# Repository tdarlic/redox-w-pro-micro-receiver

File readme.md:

# [Redox](https://github.com/mattdibi/redox-keyboard) W Pro Micro receiver

The original Redox keyboard is using receiver that consists from the Arduino Pro Micro board and custom made "shield"
that is used to put few leds and a YJ-14015 module (Core51822B clone).

This PCB uses the on board copper connection to plug directly into the computer.
 
The rest of the board can be used the same way, there is a programming port for YJ-14015 module.

## Versions

### Full version [main branch]
This is single sided PCB with few test pads on the bottom

### Mini version [mini branch]
This is double sided PCB with YJ-14015 on the bottom together with some test pads

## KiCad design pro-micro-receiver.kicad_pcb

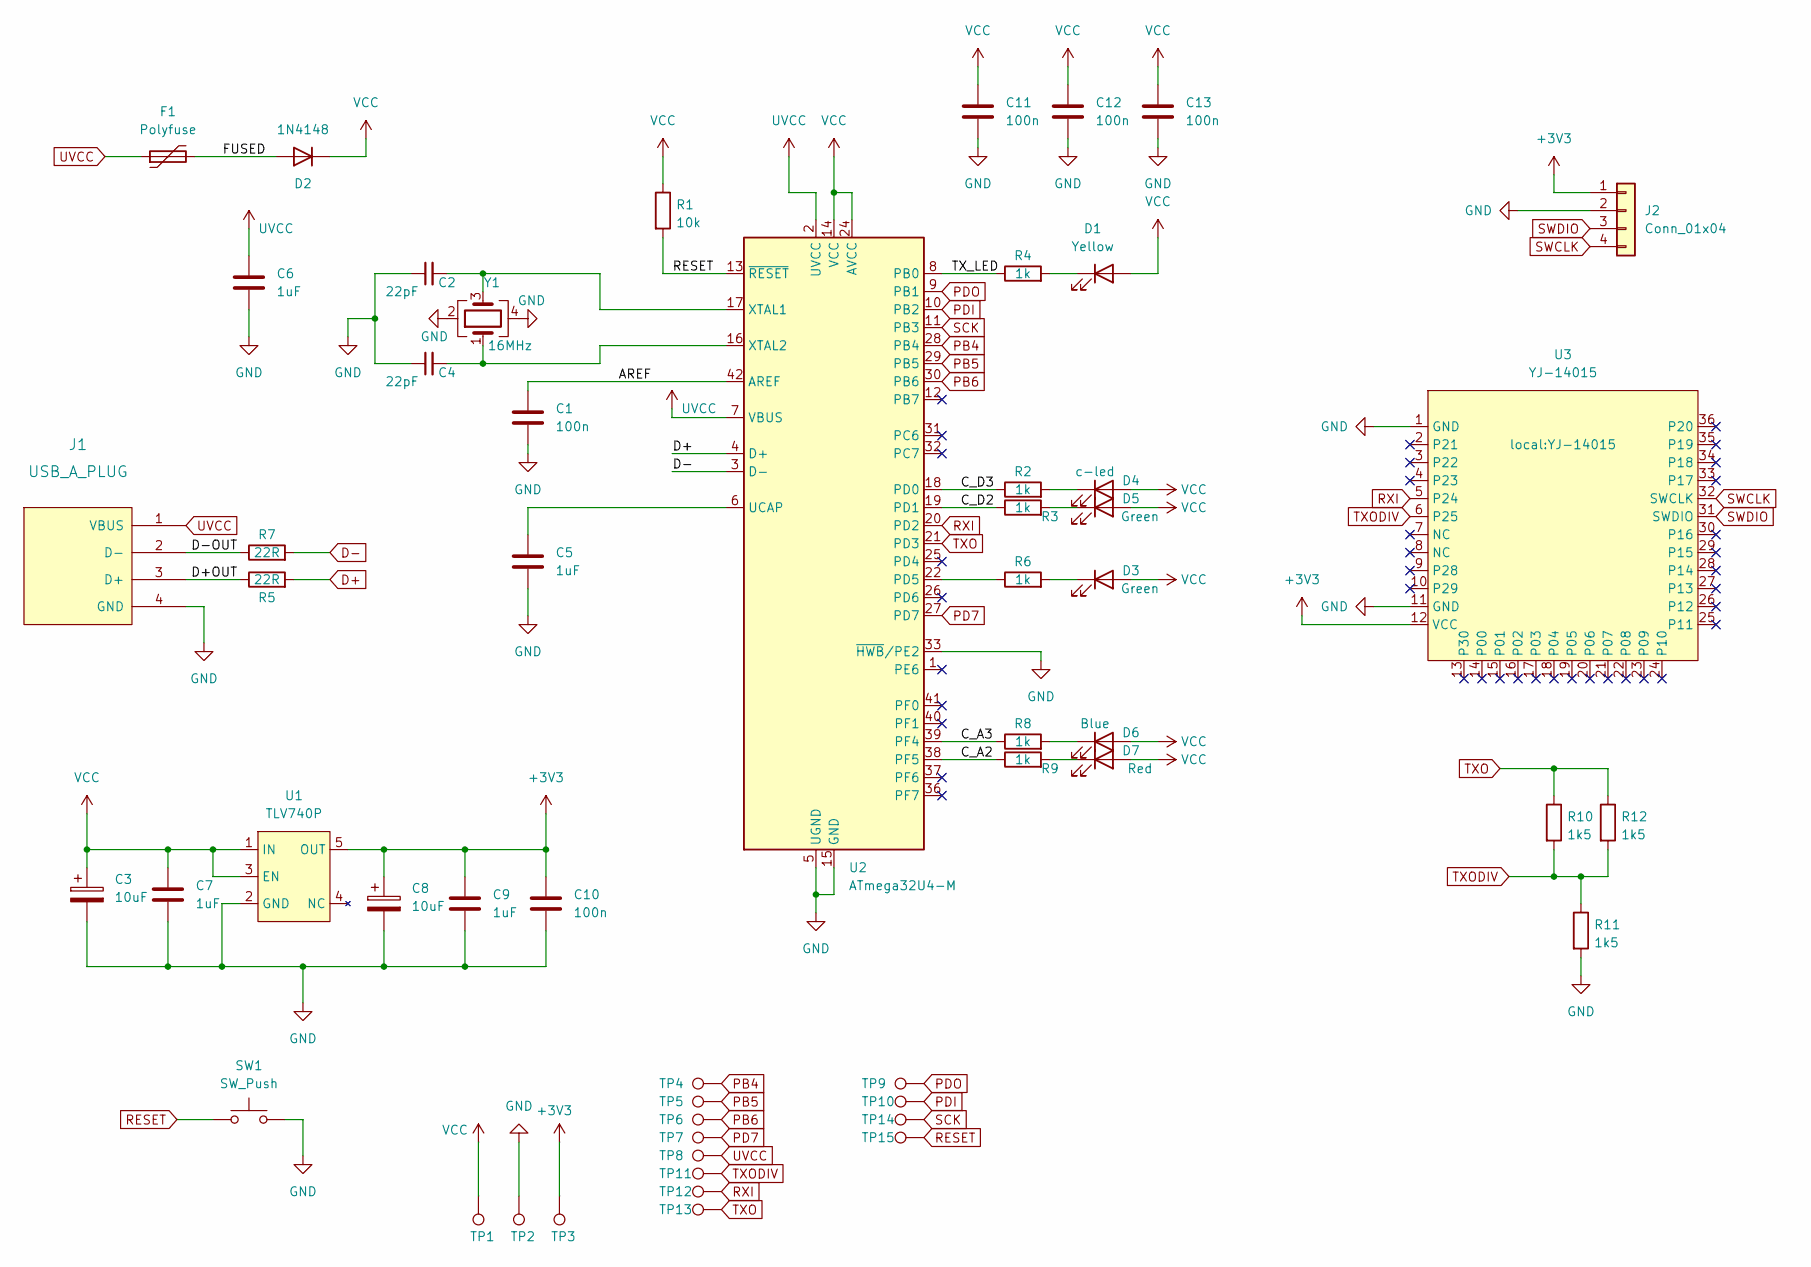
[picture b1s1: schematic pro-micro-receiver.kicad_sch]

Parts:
C1, C10, C11, C12, C13: 100n; C_0603_1608Metric
C2, C4: 22pF; C_0603_1608Metric
C3, C8: 10uF; CP_EIA-1608-10_AVX-L_Pad1.25x1.05mm
C5, C6, C7, C9: 1uF; C_0603_1608Metric
D1: Yellow; D_0603_1608Metric_Pad1.05x0.95mm
D2: 1N4148; D_SOD-123
D3, D5: Green; D_0603_1608Metric_Pad1.05x0.95mm
D4: c-led; D_0603_1608Metric_Pad1.05x0.95mm
D6: Blue; D_0603_1608Metric_Pad1.05x0.95mm
D7: Red; D_0603_1608Metric_Pad1.05x0.95mm
F1: Polyfuse; Fuse_1812_4532Metric
J1: USB_A_PLUG; usb-PCB
J2: Conn_01x04; PinHeader_1x04_P2.54mm_Vertical
R1: 10k; R_0603_1608Metric
R2, R3, R4, R6, R8, R9: 1k; R_0603_1608Metric
R5, R7: 22R; R_0603_1608Metric
R10, R11, R12: 1k5; R_0603_1608Metric
SW1: SW_Push; BZCN_TSB001A3512A
TP1, TP2, TP3, TP4, TP5, TP6, TP7, TP8, TP9, TP10, TP11, TP12, TP13, TP14, TP15: TestPoint; TestPoint_Pad_D1.5mm
U1: TLV740P; SOT-23-5
U2: ATmega32U4-M; QFN-44-1EP_7x7mm_P0.5mm_EP5.2x5.2mm
U3: YJ-14015
Y1: 16MHz; Crystal_SMD_EuroQuartz_MT-4Pin_3.2x2.5mm

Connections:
+3V3: C8.1, C9.1, C10.1, J2.1, TP3.1, U1.5 (OUT), U3.12 (VCC)
/AREF: C1.1, U2.42 (AREF)
/C_A2: R9.1, U2.38 (PF5)
/C_A3: R8.1, U2.39 (PF4)
/C_D2: R3.1, U2.19 (PD1)
/C_D3: R2.1, U2.18 (PD0)
/D+OUT: J1.3 (D+), R5.1
/D-OUT: J1.2 (D-), R7.1
/FUSED: D2.2 (A), F1.2
/TX_LED: R4.1, U2.8 (PB0)
D+: R5.2, U2.4 (D+)
D-: R7.2, U2.3 (D-)
GND: C1.2, C2.1, C3.2, C4.1, C5.2, C6.2, C7.2, C8.2, C9.2, C10.2, C11.2, C12.2, C13.2, J1.4 (GND), J2.2, R11.2, SW1.2, TP2.1, U1.2 (GND), U2.5 (UGND), U2.15 (GND), U2.23 (GND), U2.33 (~HWB/PE2), U2.35 (GND), U2.43 (GND), U2.45 (GND), U3.1 (GND), U3.11 (GND), Y1.2, Y1.4
unnamed: C2.2, U2.17 (XTAL1), Y1.3
unnamed: C4.2, U2.16 (XTAL2), Y1.1
unnamed: C5.1, U2.6 (UCAP)
unnamed: D1.1 (K), R4.2
unnamed: D3.1 (K), R6.2
unnamed: D4.1 (K), R2.2
unnamed: D5.1 (K), R3.2
unnamed: D6.1 (K), R8.2
unnamed: D7.1 (K), R9.2
unnamed: R6.1, U2.22 (PD5)
PB4: TP4.1, U2.28 (PB4)
PB5: TP5.1, U2.29 (PB5)
PB6: TP6.1, U2.30 (PB6)
PD7: TP7.1, U2.27 (PD7)
PDI: TP10.1, U2.10 (PB2)
PDO: TP9.1, U2.9 (PB1)
RESET: R1.2, SW1.1, TP15.1, U2.13 (~RESET)
RXI: TP12.1, U2.20 (PD2), U3.5 (P24)
SCK: TP14.1, U2.11 (PB3)
SWCLK: J2.4, U3.32 (SWCLK)
SWDIO: J2.3, U3.31 (SWDIO)
TXO: R10.1, R12.1, TP13.1, U2.21 (PD3)
TXODIV: R10.2, R11.1, R12.2, TP11.1, U3.6 (P25)
UVCC: C6.1, F1.1, J1.1 (VBUS), TP8.1, U2.2 (UVCC), U2.7 (VBUS)
VCC: C3.1, C7.1, C11.1, C12.1, C13.1, D1.2 (A), D2.1 (K), D3.2 (A), D4.2 (A), D5.2 (A), D6.2 (A), D7.2 (A), R1.1, TP1.1, U1.1 (IN), U1.3 (EN), U2.14 (VCC), U2.24 (AVCC), U2.34 (VCC), U2.44 (AVCC)

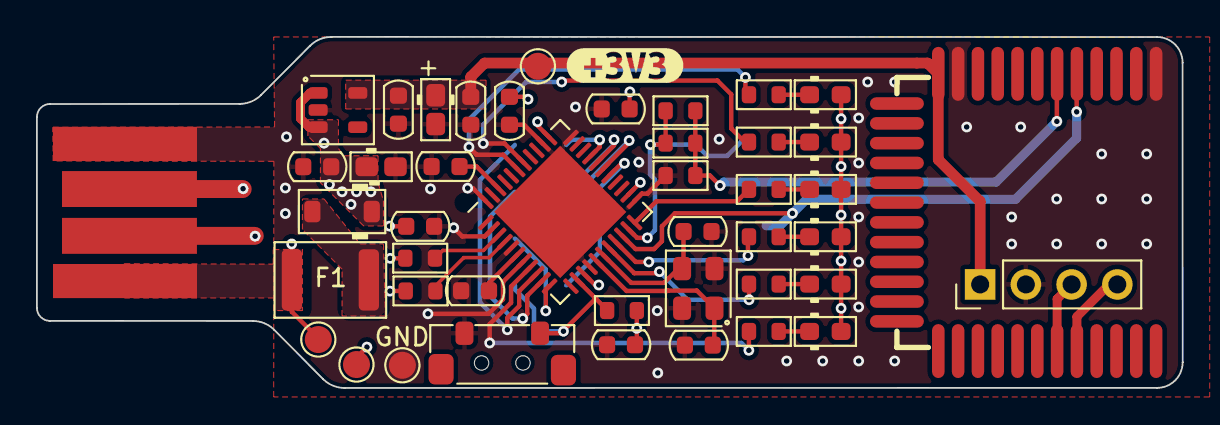
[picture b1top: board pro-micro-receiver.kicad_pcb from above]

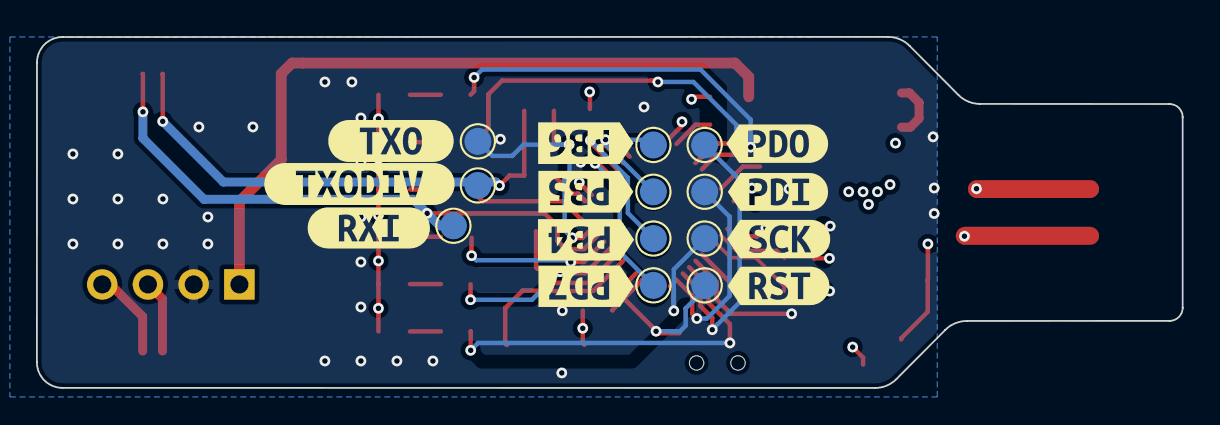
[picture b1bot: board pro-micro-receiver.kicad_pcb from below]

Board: 4 copper layers, 63.7 x 19.5 mm, 67 parts (22 on the bottom side), 38 nets.

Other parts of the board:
kibuzzard-63ACD5DB: G***; kibuzzard-63ACD5DB
kibuzzard-63ACD5FF: G***; kibuzzard-63ACD5FF
kibuzzard-63ACD69E: G***; kibuzzard-63ACD69E
kibuzzard-63ACD615: G***; kibuzzard-63ACD615
kibuzzard-63ACD627: G***; kibuzzard-63ACD627
kibuzzard-63ACD667: G***; kibuzzard-63ACD667
kibuzzard-63ACD680: G***; kibuzzard-63ACD680
kibuzzard-63BC8742: G***; kibuzzard-63BC8742
kibuzzard-63F7D9D7: G***; kibuzzard-63F7D9D7
kibuzzard-63F7D9F1: G***; kibuzzard-63F7D9F1
kibuzzard-63F7DA1C: G***; kibuzzard-63F7DA1C
kibuzzard-63F7DA07: G***; kibuzzard-63F7DA07

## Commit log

2022-12-27 Adding existing files to a project - initial commit
2022-12-27 Adding backup dir to gitignore and removing backup dir
2022-12-27 Fixing the stackup Adding initial board outline Moving all elements onto the board
2022-12-27 Adding readme
2022-12-27 Fixing title
2022-12-27 Shortening the board and better placement of components
2022-12-27 Small change in readme
2022-12-28 Compacting the board
    Shifting the crystal and the components to shorten the board
    Distancing the elements from the edge
    Rounding the corners
2022-12-28 Completed routing board
    Removed all designators from silkscreen
2022-12-28 Adding testpoints in schematic
2022-12-28 Adding testpoints to PCB
2022-12-28 Adding flags for testpoints
2022-12-29 Small fixes on the PCB
2022-12-29 Completed routing minified PCB
    Passing DRC, tested gerbers on Aisler web
2022-12-29 Adding images folder
2022-12-29 Adding images from main to this branch
2022-12-29 Adding comments and images to readme
2022-12-29 Copying the readme.md from main
2022-12-29 Adding missing values for resistors
2022-12-29 Adding missing resistor values
2022-12-29 Making some traces thicker on the bottom copper
2023-01-09 Minor changes on the mini board
2023-01-09 Adding labels to +3V3 and GND testpoints
2023-02-23 Adding BOM for assembly and programming port on the back
